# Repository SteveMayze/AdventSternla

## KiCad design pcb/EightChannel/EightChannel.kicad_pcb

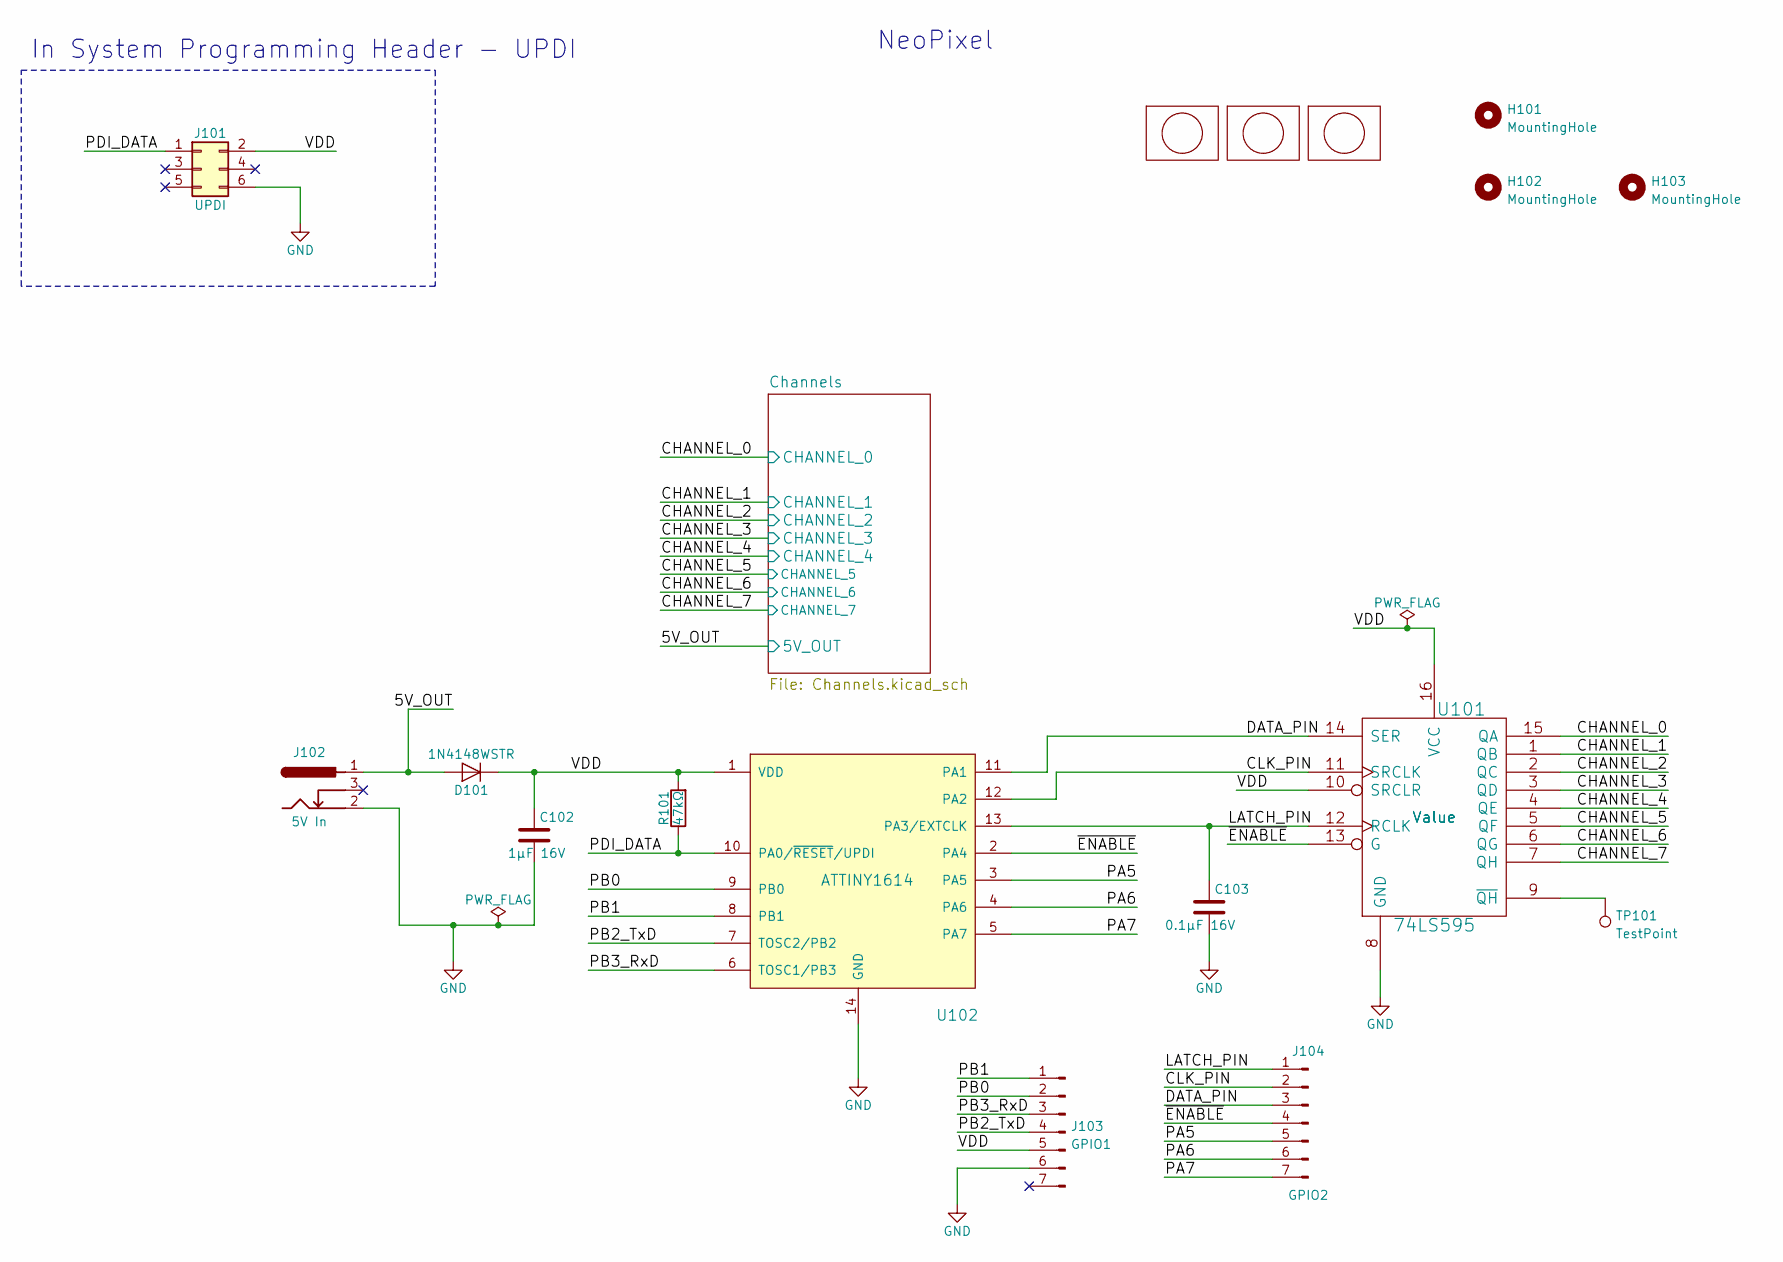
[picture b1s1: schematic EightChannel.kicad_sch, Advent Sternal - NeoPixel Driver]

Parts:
C102: 1μF 16V; C_0805_HandSoldering
C103: 0.1μF 16V; C_0805_HandSoldering
D101: 1N4148WSTR; D_SOD-123F; MPN 1N4148WSTR
H101, H102, H103: MountingHole; MountingHole_2.7mm_M2.5
J101: UPDI; PRG_TC2030-IDC-NL
J102: 5V In; CONN_PWR_JACK_1_3X3_5MM_SOLDER; MPN PJ-031DH
J103: GPIO1; PinHeader_1x07_P2.54mm_Vertical
J104: GPIO2; PinHeader_1x07_P2.54mm_Vertical
Lg101: logo; MyBasic_rounded_50_1
Lg102: logo; KiCad-Logo2_5mm_SilkScreen
Lg103: logo; QR_AdventSternla_FS
R101: 47kΩ; R_0805_2012Metric
TP101: TestPoint; TestPoint_THTPad_D1.0mm_Drill0.5mm
U101: 74LS595; SOIC-16_3.9x9.9mm_Pitch1.27mm; MPN Value
U102: ATTINY1614; SOIC-14_3.9x8.7mm_P1.27mm

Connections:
/5V_OUT: D101.2 (A), J102.1; also elsewhere on the board
/CHANNEL_0: U101.15 (QA); also elsewhere on the board
/CHANNEL_1: U101.1 (QB); also elsewhere on the board
/CHANNEL_2: U101.2 (QC); also elsewhere on the board
/CHANNEL_3: U101.3 (QD); also elsewhere on the board
/CHANNEL_4: U101.4 (QE); also elsewhere on the board
/CHANNEL_5: U101.5 (QF); also elsewhere on the board
/CHANNEL_6: U101.6 (QG); also elsewhere on the board
/CHANNEL_7: U101.7 (QH); also elsewhere on the board
/CLK_PIN: J104.2, U101.11 (SRCLK), U102.12 (PA2)
/DATA_PIN: J104.3, U101.14 (SER), U102.11 (PA1)
/LATCH_PIN: C103.1, J104.1, U101.12 (RCLK), U102.13 (PA3/EXTCLK)
/PA5: J104.5, U102.3 (PA5)
/PA6: J104.6, U102.4 (PA6)
/PA7: J104.7, U102.5 (PA7)
/PB0: J103.2, U102.9 (PB0)
/PB1: J103.1, U102.8 (PB1)
/PB2_TxD: J103.4, U102.7 (TOSC2/PB2)
/PB3_RxD: J103.3, U102.6 (TOSC1/PB3)
/PDI_DATA: J101.1, R101.1, U102.10 (PA0/~RESET/UPDI)
/VDD: C102.1, D101.1 (K), J101.2, J103.5, R101.2, U101.10 (SRCLR), U101.16 (VCC), U102.1 (VDD)
/~ENABLE: J104.4, U101.13 (G), U102.2 (PA4)
GND: C102.2, C103.2, J101.6, J102.2, J103.6, U101.8 (GND), U102.14 (GND); also elsewhere on the board
unnamed: TP101.1, U101.9 (~QH)

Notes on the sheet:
NeoPixel
In System Programming Header - UPDI

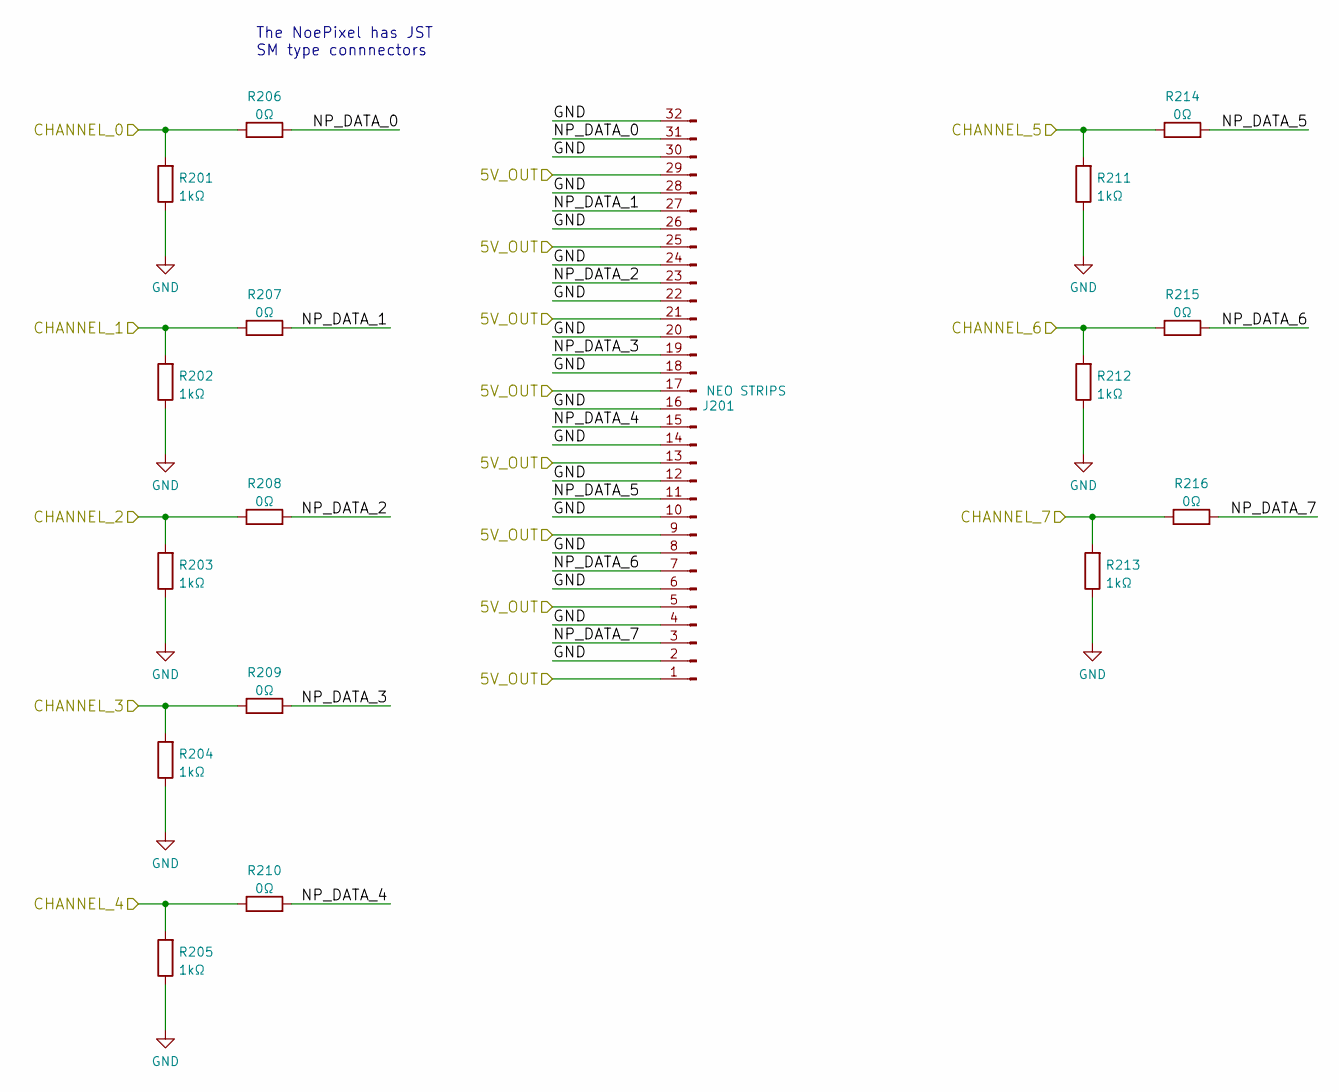
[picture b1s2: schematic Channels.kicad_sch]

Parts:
J201: NEO STRIPS; PinHeader_2x16_P2.54mm_Horizontal
R201, R202, R203, R204, R205, R211, R212, R213: 1kΩ; R_0805_2012Metric
R206, R207, R208, R209, R210, R214, R215, R216: 0Ω; R_0805_2012Metric

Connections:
/5V_OUT: J201.1, J201.5, J201.9, J201.13, J201.17, J201.21, J201.25, J201.29; also elsewhere on the board
/CHANNEL_0: R201.2, R206.1; also elsewhere on the board
/CHANNEL_1: R202.2, R207.1; also elsewhere on the board
/CHANNEL_2: R203.2, R208.1; also elsewhere on the board
/CHANNEL_3: R204.2, R209.1; also elsewhere on the board
/CHANNEL_4: R205.2, R210.1; also elsewhere on the board
/CHANNEL_5: R211.2, R214.1; also elsewhere on the board
/CHANNEL_6: R212.2, R215.1; also elsewhere on the board
/CHANNEL_7: R213.2, R216.1; also elsewhere on the board
/Channels/NP_DATA_0: J201.31, R206.2
/Channels/NP_DATA_1: J201.27, R207.2
/Channels/NP_DATA_2: J201.23, R208.2
/Channels/NP_DATA_3: J201.19, R209.2
/Channels/NP_DATA_4: J201.15, R210.2
/Channels/NP_DATA_5: J201.11, R214.2
/Channels/NP_DATA_6: J201.7, R215.2
/Channels/NP_DATA_7: J201.3, R216.2
GND: J201.2, J201.4, J201.6, J201.8, J201.10, J201.12, J201.14, J201.16, J201.18, J201.20, J201.22, J201.24, J201.26, J201.28, J201.30, J201.32, R201.1, R202.1, R203.1, R204.1, R205.1, R211.1, R212.1, R213.1; also elsewhere on the board

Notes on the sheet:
The NoePixel has JST SM type connnectors

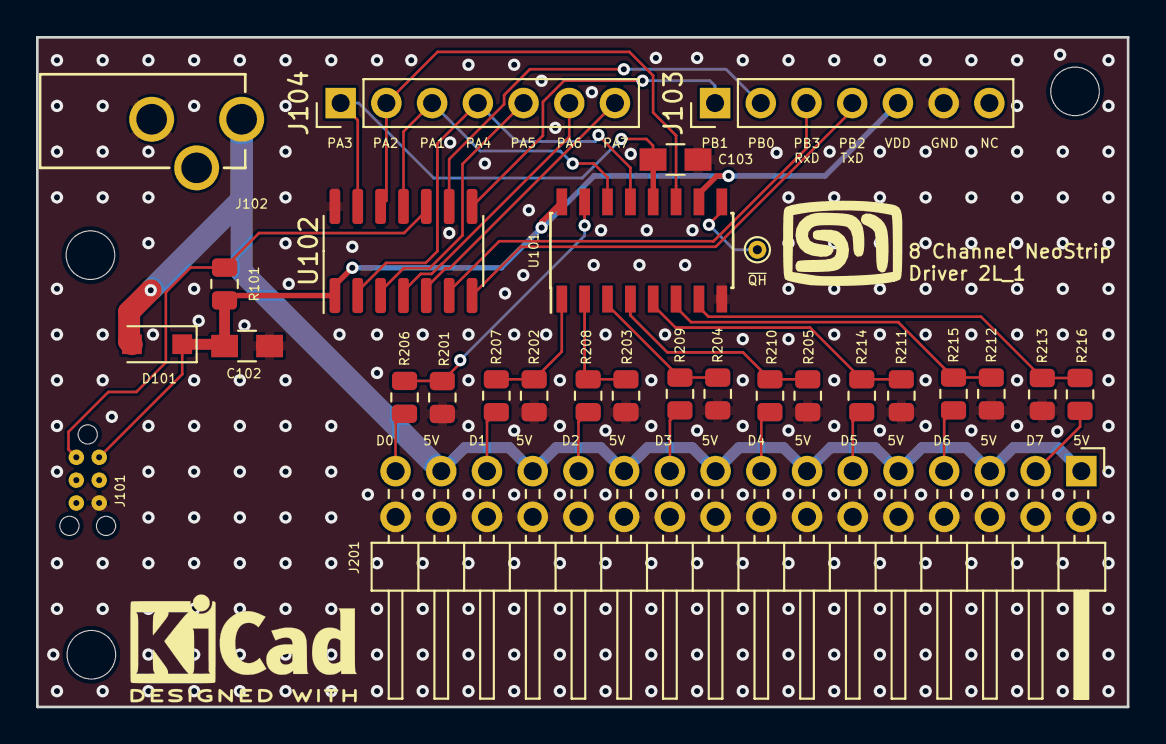
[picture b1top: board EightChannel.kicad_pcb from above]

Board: 2 copper layers, 60.6 x 37.2 mm, 34 parts (1 on the bottom side), 32 nets.

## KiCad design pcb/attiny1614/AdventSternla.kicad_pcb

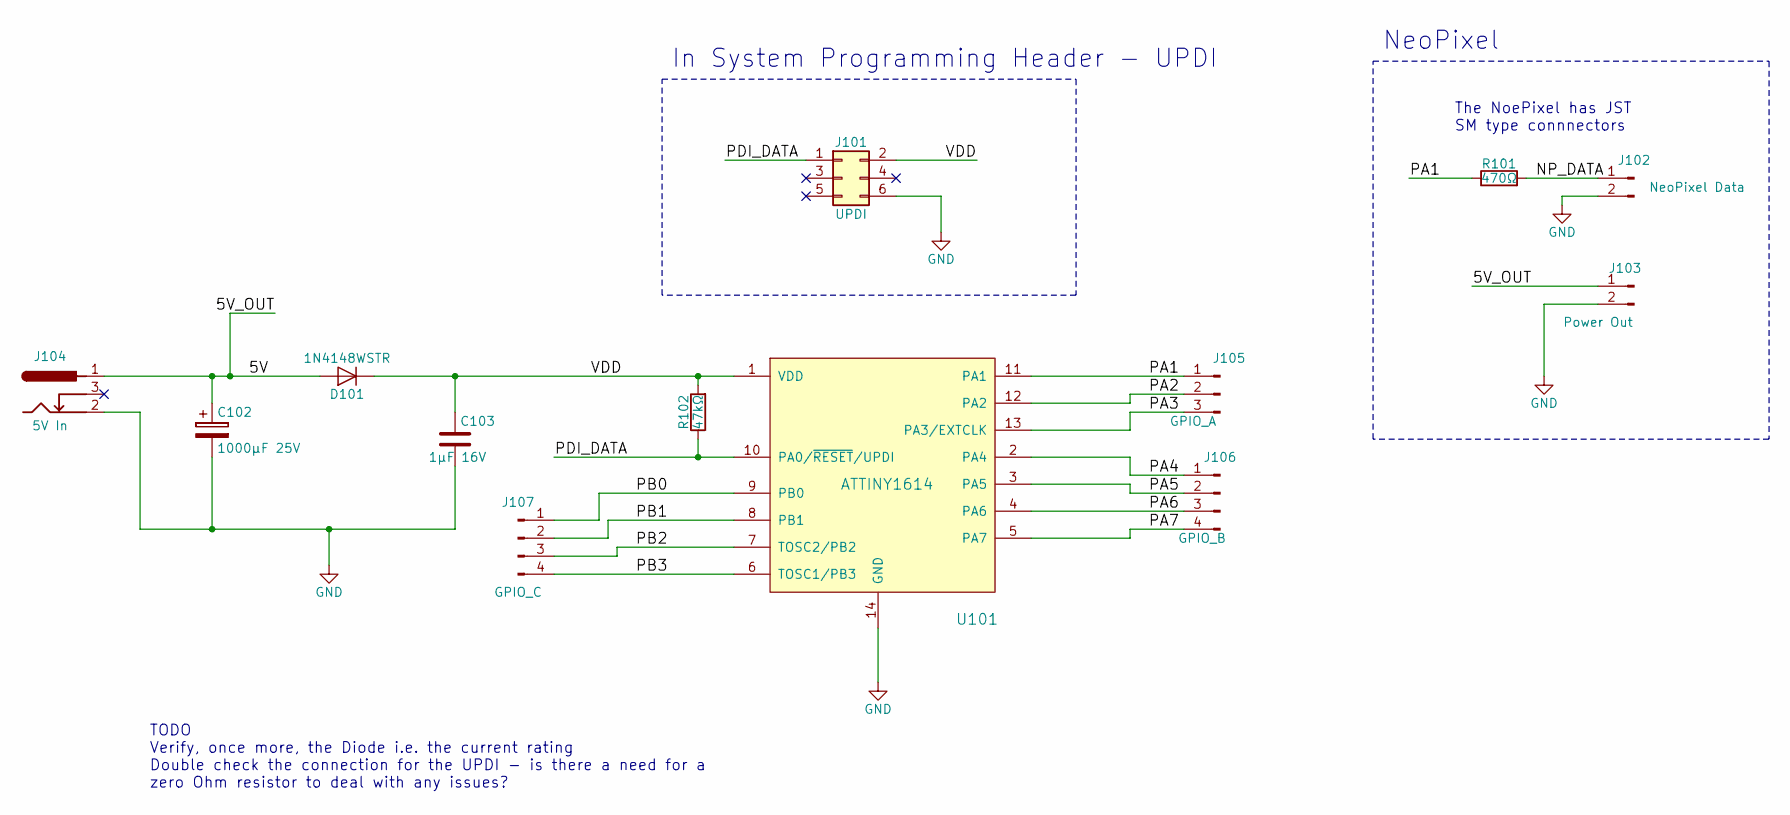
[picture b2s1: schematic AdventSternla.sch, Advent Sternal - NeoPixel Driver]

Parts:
C102: 1000μF 25V; CP_Radial_L21.0mm_D13.0mm_P5.00mm_Horizontal
C103: 1μF 16V; C_0805_HandSoldering
D101: 1N4148WSTR; D_SOD-123F; MPN 1N4148WSTR
J101: UPDI; PRG_TC2030-IDC-NL
J102: NeoPixel Data; Pin_Header_Straight_1x02_Pitch2.54mm
J103: Power Out; Pin_Header_Straight_1x02_Pitch2.54mm
J104: 5V In; CONN_PWR_JACK_1_3X3_5MM_SOLDER; MPN PJ-031DH
J105: GPIO_A; Pin_Header_Straight_1x03_Pitch2.54mm
J106: GPIO_B; Pin_Header_Straight_1x04_Pitch2.54mm
J107: GPIO_C; Pin_Header_Straight_1x04_Pitch2.54mm
R101: 470Ω; R_0805_HandSoldering
R102: 47kΩ; R_0805_HandSoldering
U101: ATTINY1614; SOIC-14_N

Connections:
/5V: C102.1, D101.2 (A), J103.1, J104.1
/NP_DATA: J102.1, R101.2
/PA1: J105.1, R101.1, U101.11 (PA1)
/PA2: J105.2, U101.12 (PA2)
/PA3: J105.3, U101.13 (PA3/EXTCLK)
/PA4: J106.1, U101.2 (PA4)
/PA5: J106.2, U101.3 (PA5)
/PA6: J106.3, U101.4 (PA6)
/PA7: J106.4, U101.5 (PA7)
/PB0: J107.1, U101.9 (PB0)
/PB1: J107.2, U101.8 (PB1)
/PB2: J107.3, U101.7 (TOSC2/PB2)
/PB3: J107.4, U101.6 (TOSC1/PB3)
/PDI_DATA: J101.1, R102.1, U101.10 (PA0/~RESET~/UPDI)
/VDD: C103.1, D101.1 (K), J101.2, R102.2, U101.1 (VDD)
GND: C102.2, C103.2, J101.6, J102.2, J103.2, J104.2, U101.14 (GND)

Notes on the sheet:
In System Programming Header - UPDI
The NoePixel has JST SM type connnectors
NeoPixel
TODO Verify, once more, the Diode i.e. the current rating Double check the connection for the UPDI - is there a need for a zero Ohm resistor to deal with any issues?

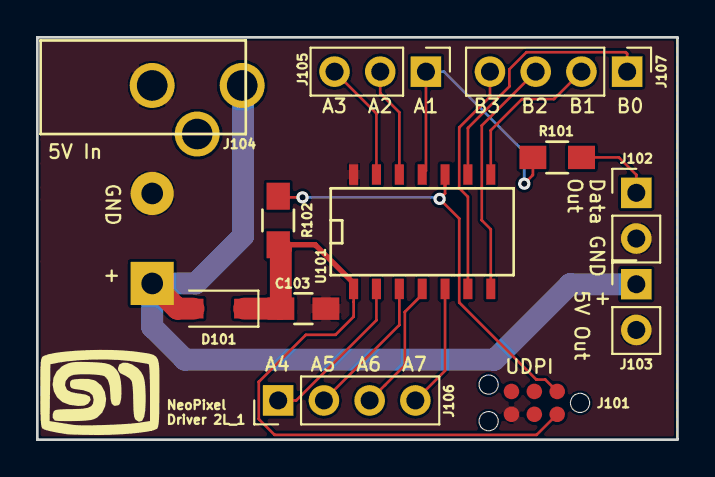
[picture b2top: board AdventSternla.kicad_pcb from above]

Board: 2 copper layers, 35.6 x 22.4 mm, 13 parts (1 on the bottom side), 16 nets.

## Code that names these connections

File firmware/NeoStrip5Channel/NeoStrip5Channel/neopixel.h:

#ifndef INCLUDE_NEOPIXEL_H
#define INCLUDE_NEOPIXEL_H

#include <avr/io.h>
#include <stdbool.h>
#include "attiny1614_sr595.h"

/*! The port pin PA1 */
#define NEOPIXEL_PA1 1
/*! The port pin PA2 */
#define NEOPIXEL_PA2 2
/*! The port pin PA3 */
#define NEOPIXEL_PA3 3
/*! The port pin PA4 */
#define NEOPIXEL_PA4 4
/*! The port pin PA5 */
#define NEOPIXEL_PA5 5
/*! The port pin PA6 */
#define NEOPIXEL_PA6 6
/*! The port pin PA7 */
#define NEOPIXEL_PA7 7


/*! The port for the neopixel and shift register */
#define NEOPIXEL_PORT VPORTA_OUT

/*! The output port pin for driving the NeoPixel strip */
#define NEOPIXEL_NEOPIN SR595_ENABLE

/*! The number of NeoPixels */
#define neopixel_pixels 60

/*! The NeoPixel buffer size */
#define neopixel_buffer_size neopixel_pixels * 3
/*! The location of the first pixel */
#define FIRST_PIXEL 0
/*! The location of the last pixel */
#define LAST_PIXEL ((neopixel_pixels-1) *3)

/*! The relative location of the RED colour data */
#define NEO_RED 1
/*! The relative location of the GREEN colour data */
#define NEO_GREEN 0
/*! The relative location of the BLUE colour data */
#define NEO_BLUE 2


/*! The highest intensity for a pixel colour i.e. ON*/
#define NEO_ALL_ON 0xFF
/*! The lowest intensity for a pixel colour i.e OFF */
#define NEO_ALL_OFF 0x00


void delay_ms(int ms);

void neopixel_init();

/*!
 * \brief	Sets a pixel with the RGB code
 */
void neopixel_setPixel(uint8_t pixel, uint8_t red, uint8_t green, uint8_t blue);

/*!
 * \brief	Shifts the pixels one pixel in the indicated direction
 */
void neopixel_shift( bool direction );

/*!
 * \brief	Initialises the buffer with the given colour 
 */
void neopixel_fill(uint8_t red, uint8_t green, uint8_t blue);

/*!
 * \brief Pushes the buffer out to the pixel strip.
 */
void neopixel_show();

void neopixel_setchannel( uint8_t channel );

#endif 

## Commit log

2017-10-23 Adding an initial Schematic
2017-10-24 Schematic for the attiny1614 version
2017-10-25 Schematic is done and started the layout
2017-10-29 Correction to power filtering
2017-11-01 Annotated the changes to the power filtering
2017-11-02 Initial layout completed
2017-11-02 Added some more nomenclature for the pin headers
2017-11-17 Added Gerbers and sent to OSH Park
2017-12-14 Corrected the diode foot print as with the power jack
2017-12-17 Bringing up the board - Schematic change and Clock Check Firmware
    Bringing up the board, it was found that the stabilising capacitor was
    not needed. A Blinky was created to verify the clock speed and work out
    how to set it to the full 20MHz.
2017-12-22 Inital try at the firmware
2017-12-22 Further on the firmware - still need to get the phasing corrected
2017-12-22 Starting to tune the settings
2017-12-23 Still trying to find the right duty cycle
2017-12-24 Still tuning
2017-12-25 Third Algorithm attempt
2017-12-25 Added a third and fourth algorithm
2017-12-26 Finally a working algorithm
2017-12-31 Added some more animations
2017-12-31 testing
2018-01-01 New animation and sequence
2018-01-01 A final animation sequence and Doxygen annotations and generated files
2018-01-04 Made the layout change for the unneeded C101
2018-01-10 Fixed up the diode foot print
2018-01-18 Added .DS_Store to gitignore
2018-01-18 Started a new design for a 5 channel NoePixel driver
2018-01-18 Filled out the schematic for the five channels
2018-01-19 Started the layout
2018-01-21 Working through the five channel prototype layout
2018-01-22 Finished the layout and sent to OSH Park
2018-01-30 Just adding the Gerbers
2018-02-04 Experimented with the firmware for further animiations ideas
2018-02-10 Starting the 5 channel firmware
2018-02-11 Getting the five channle firmware working
2018-02-12 All five channels are working
2018-02-13 Refactored the code to be more modular ... one step of more
2018-02-13 Multichanel, multibuffer firmware v1 done.
2018-03-06 Fixed some issues with the anim_wipe and added some more animations
2018-11-24 Added the driver for the tree lights
2018-11-24 Adds the ignore for the Release profile files
2018-11-24 Alters the timing of the intensity
2018-12-22 Added a 5m strip driver
2018-12-22 Set up to use a given buffer and reorganised the code
2018-12-22 Update to KiCAD 5
2018-12-22 Removing the NeoStrip5M from this branch
2018-12-22 Adds support for the 5m Neopixel Strip - 150
2018-12-25 Corrects a small issue with the stars
2019-12-15 Fixed some issues with the star generation and shut down
2019-12-15 A few more adjustments along with the number of stars
2019-12-17 Correction to the ramp-down since some pixels were reported as active though they were off
2019-12-23 More adjustments and an additional project for troubleshooting
2019-12-26 Small changes for troublshooting
2019-12-26 Fixes the issue with the reducing star numbers
2021-12-12 Refresh
2022-06-12 Adds an 8 channel text display design
2022-06-13 Schematic updates
2022-06-22 Intermediate
2022-06-23 Finished 8Channel and submitted to Fab
2025-01-11 Update to the stars - adding a comment
2025-01-11 Restore the default length to long
2025-01-12 Basic setup for configurable builds for testing
2025-01-27 Stars with commet
2025-01-27 Commet 5m (#1)
    * Basic setup for configurable builds for testing
    * Stars with commet
    ---------
2025-02-01 Restores the 5 channel PCB design and updates to KiCad 5
2025-02-01 Hard merge of 5 channel restore
2025-02-01 Hard merge of 5 channel restore (#4)
2025-02-01 Update and synch of the eight channel design
2025-02-01 Update to the git ignore
